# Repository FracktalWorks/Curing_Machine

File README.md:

# Curing_Machine
#Development Documentation:
## Setting up Raspberry Pi:
### Writing Image: 
[Raspbian Buster Lite](https://downloads.raspberrypi.org/raspbian_lite/images/raspbian_lite-2020-02-14/)

[Win32 Disk Imager](https://sourceforge.net/projects/win32diskimager/files/latest/download)

[SD Card Formatter](https://www.sdcard.org/downloads/formatter/sd-memory-card-formatter-for-windows-download/)

Clean with disk with SD card formatter selecting Quick Format and write Image to SD Card

### Setting up Pi
Add Wireless Settings & Enable SSH:
[link](https://www.tomshardware.com/reviews/raspberry-pi-headless-setup-how-to,6028.html)

```
country=IN
ctrl_interface=DIR=/var/run/wpa_supplicant GROUP=netdev
update_config=1

network={
scan_ssid=1
ssid="Fracktal 5"
psk="******"
}
```
WPA Supplicant known to work

### Installing dependencies
run ```sudo apt-get update --allow-releaseinfo-change``` in case of issues installing

pip3: ```sudo apt-get install python3-pip```

PyQt5: ```sudo apt-get install qt5-default pyqt5-dev pyqt5-dev-tools```

PyQT5: ```sudo apt install python3-pyqt5```

Git: ```sudo apt-get install git```

### Install 3.5inch touch screen driver

Reference: [link](https://www.waveshare.com/wiki/3.5inch_RPi_LCD_(A))

run: 
```
git clone https://github.com/waveshare/LCD-show.git
cd LCD-show
ls
chmod +x LCD35-show
./LCD35-show
```

### To make LCD Faster (Issue with ili based screens)

Changed ```sudo nano /boot/config.txt``` bottom to:

```
# Enable audio (loads snd_bcm2835)
dtparam=audio=on
dtoverlay=waveshare35a,fps=12,speed=16000000
#dtoverlay=ads7846,cs=1,penirq=17,penirq_pull=2,speed=1000000,keep_vref_on=1,swapxy=1,pmax=255,xohm$
hdmi_force_hotplug=1
#max_usb_current=1
hdmi_group=2
#hdmi_mode=1
hdmi_mode=87
hdmi_cvt 480 320 12 6 0 0 0
hdmi_drive=2
```
### Install Xwindows

```sudo apt-get install xserver-xorg-video-fbdev```

```sudo apt-get install xserver-xorg```

```sudo apt-get install xinit```

```sudo apt-get install x11-xserver-utils```

```sudo mv /usr/share/X11/xorg.conf.d/99-fbturbo.conf ~```  see [link](https://learn.adafruit.com/adafruit-pitft-3-dot-5-touch-screen-for-raspberry-pi/faq) for more information on this step

To test out working, use the following to start a PyQt5 program with ```sudo startx```
```#!/bin/sh

# /etc/X11/xinit/xinitrc
#
# global xinitrc file, used by all X sessions started by xinit (startx)
cd /home/pi/Julia2018Octoprint/venv/lib/python2.7/site-packages/octoprint_Julia2018ProDualABLTouchUI
sudo chmod +x Main.py
sudo python3 Main.py
# invoke global X session script
. /etc/X11/Xsession
```
###Removing boot messages
```sudo nano /boot/cmdline.txt```
change ```console=tty1``` to ```console=tty3``` 
Add ```loglevel=3``` to disable non-critical kernel log messages.
Add ```logo.nologo``` to the end of the line to remove the Raspberry PI logos from displaying
Press CTRL+X to exit and Y to save your changes.

### Changing the boot screen logo
Refeance : [link](https://www.hackster.io/kamaluddinkhan/changing-the-splash-screen-on-your-raspberry-pi-7aee31)
[link](https://raspberrypi.stackexchange.com/questions/100371/raspbian-buster-lite-splash-screen-instead-of-boot-messages-on-pi-3-model-b-a02)

The pi boots with a rainbow colour and many messages will be displayed during boot up.
to disable the boot message go to 
```sudo nano /boot/cmdline.txt```

in that file 
Add ```loglevel=3``` to disable non-critical kernel log messages.
Add ```logo.nologo``` to the end of the line to remove the Raspberry PI logos from displaying

now messages will not be shown 

### To add our logo 
install fbi
```sudo apt-get install fbi```

Create the file ```sudo nano /etc/systemd/system/splashscreen.service``` with the following content:

```
[Unit] 
Description=Splash screen 
DefaultDependencies=no 
After=local-fs.target 

[Service] 
ExecStart=/usr/bin/fbi -d /dev/fb0 --noverbose -a /home/pi/splash.png >/dev/null 2>&1
StandardInput=tty 
StandardOutput=tty 
[Install] 
WantedBy=sysinit.target

```
Replace `````/opt/splash.png````` with the path to the splash screen image as appropriate.

Enable the service to be run at boot by running as root:

```sudo systemctl enable splashscreen```

### Touch UI
install dependencies under ```sudo pip3```

#### Configure Startx (Xwindow manager which helps to show GUI on Raspbian os lite)

```sudo nano /etc/rc.local```
Add “startx” just before exit 0
```sudo nano /etc/X11/xinit/xinitrc```
Here you have to add the location of touch ui where it is saved and file name
Example 
```

#!/bin/sh

# /etc/X11/xinit/xinitrc
#
# global xinitrc file, used by all X sessions started by xinit (startx)
git clone https://github.com/FracktalWorks/Curing_Machine.git
cd /home/pi/Curing_Machine/code
sudo chmod +x curingMachine.py
sudo python3 curingMachine.py
# invoke global X session script
. /etc/X11/Xsession

```
Now when you do startx the GUI will boot up

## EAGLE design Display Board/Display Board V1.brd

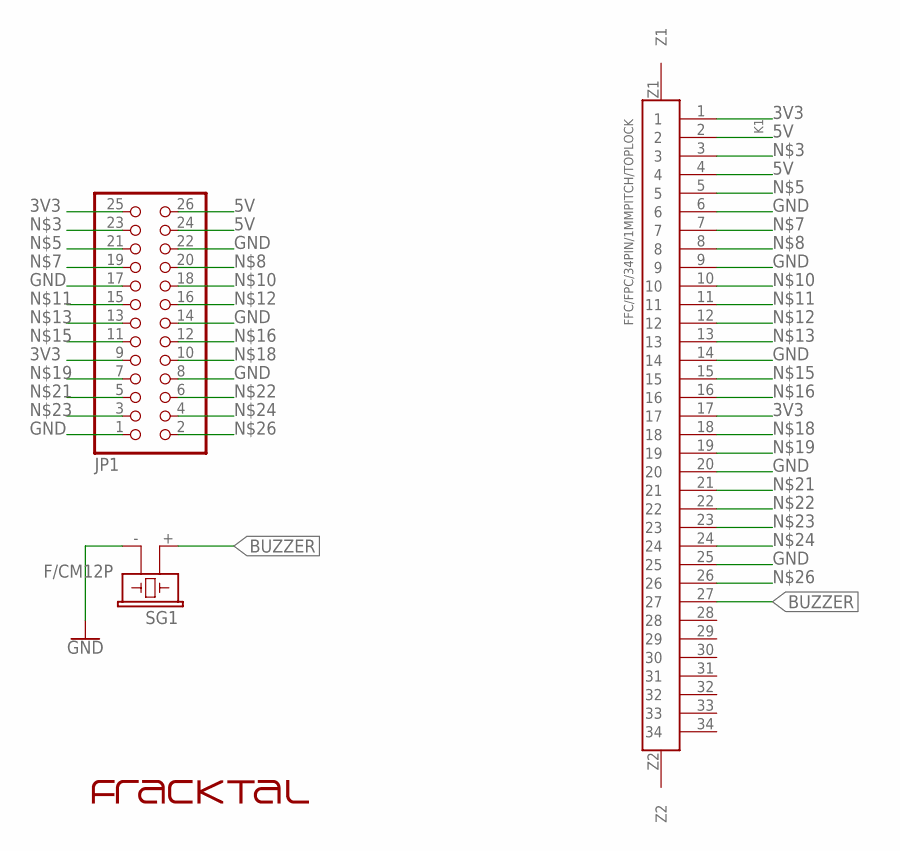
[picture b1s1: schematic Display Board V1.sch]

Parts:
JP1: PINHD-2X13; 2X13
K1: FFC/FPC/34PIN/1MMPITCH/TOPLOCK
SG1: F/CM12P
U$1: FRACKTALLOGO

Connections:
3V3: JP1.9, JP1.25, K1.1, K1.17
5V: JP1.24, JP1.26, K1.2, K1.4
BUZZER: K1.27, SG1.+ (1)
GND: JP1.1, JP1.8, JP1.14, JP1.17, JP1.22, K1.6, K1.9, K1.14, K1.20, K1.25, SG1.- (2)
unnamed: JP1.23, K1.3
unnamed: JP1.21, K1.5
unnamed: JP1.19, K1.7
unnamed: JP1.20, K1.8
unnamed: JP1.18, K1.10
unnamed: JP1.15, K1.11
unnamed: JP1.16, K1.12
unnamed: JP1.13, K1.13
unnamed: JP1.11, K1.15
unnamed: JP1.12, K1.16
unnamed: JP1.10, K1.18
unnamed: JP1.7, K1.19
unnamed: JP1.5, K1.21
unnamed: JP1.6, K1.22
unnamed: JP1.3, K1.23
unnamed: JP1.4, K1.24
unnamed: JP1.2, K1.26

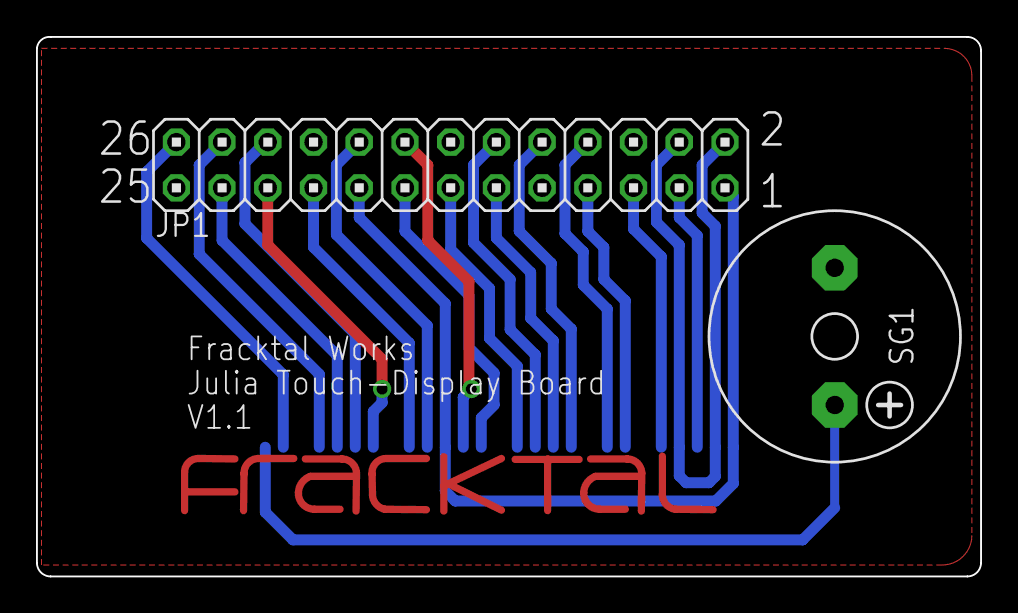
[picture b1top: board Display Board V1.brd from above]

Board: 2 copper layers, 52.5 x 30.0 mm, 4 parts (1 on the bottom side), 21 nets.

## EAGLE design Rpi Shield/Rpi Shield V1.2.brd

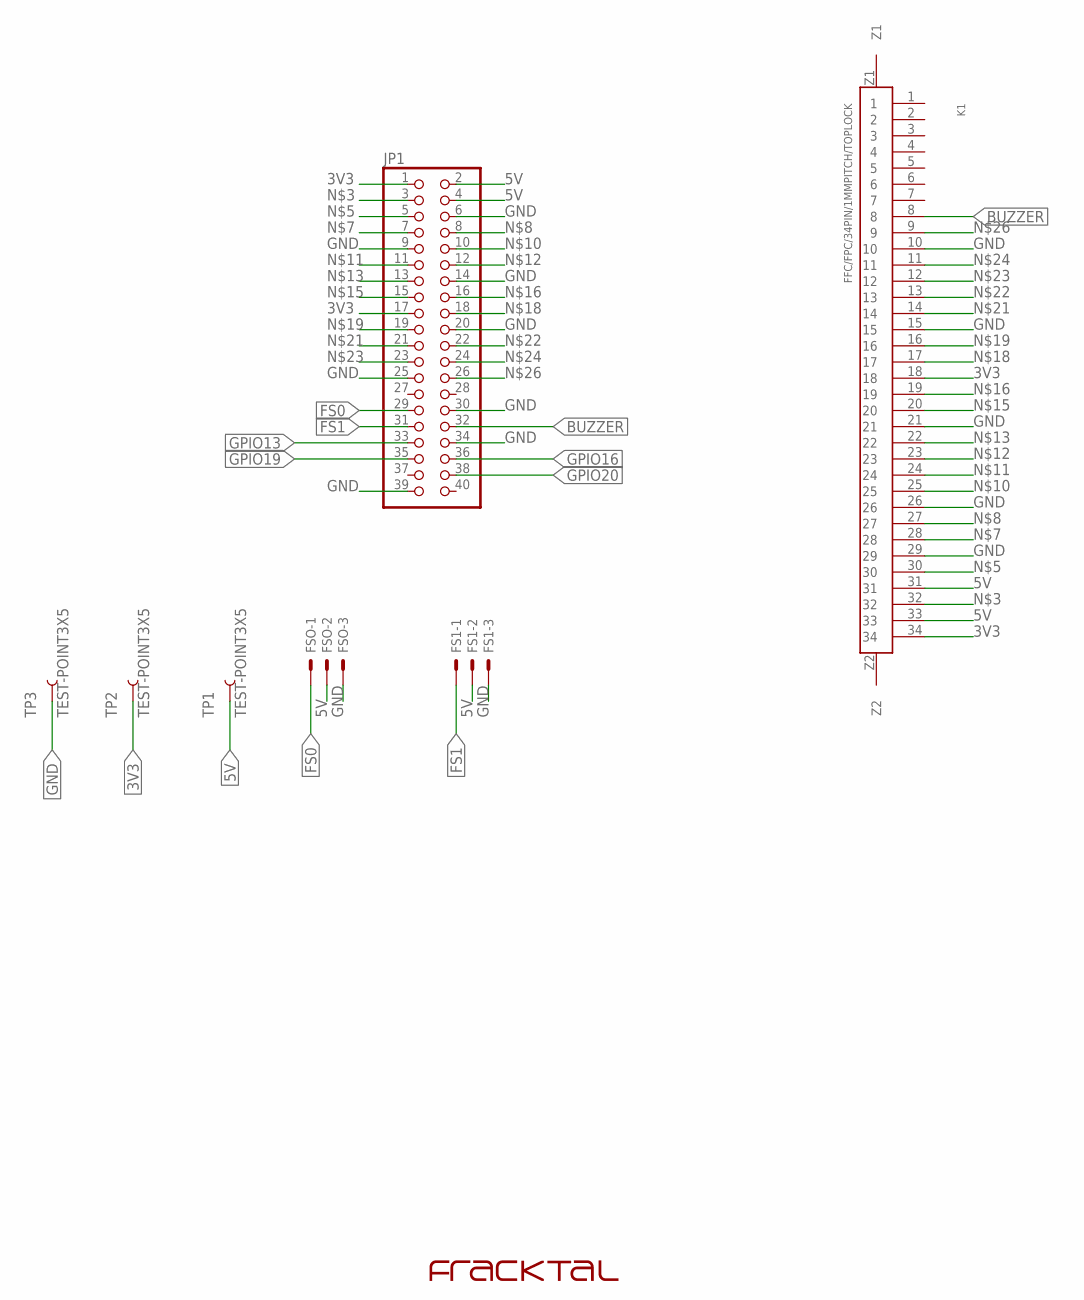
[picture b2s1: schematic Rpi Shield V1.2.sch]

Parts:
FS1: JST-XH-03-PIN-LONG-PAD; JST-XH-03-PACKAGE-LONG-PAD
FSO: JST-XH-03-PIN-LONG-PAD; JST-XH-03-PACKAGE-LONG-PAD
JP1: RASPBERRYPI_3B_GPIO
K1: FFC/FPC/34PIN/1MMPITCH/TOPLOCK
TP1, TP2, TP3: TEST-POINT3X5; PAD.03X.05
U$1: FRACKTALLOGO

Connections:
3V3: JP1.1, JP1.17, K1.18, K1.34, TP2.P$1
5V: FS1.2, FSO.2, JP1.2, JP1.4, K1.31, K1.33, TP1.P$1
BUZZER: JP1.32, K1.8
FS0: FSO.1, JP1.29
FS1: FS1.1, JP1.31
GND: FS1.3, FSO.3, JP1.6, JP1.9, JP1.14, JP1.20, JP1.25, JP1.30, JP1.34, JP1.39, K1.10, K1.15, K1.21, K1.26, K1.29, TP3.P$1
GPIO13: JP1.33
GPIO16: JP1.36
GPIO19: JP1.35
GPIO20: JP1.38
unnamed: JP1.3, K1.32
unnamed: JP1.5, K1.30
unnamed: JP1.7, K1.28
unnamed: JP1.8, K1.27
unnamed: JP1.10, K1.25
unnamed: JP1.11, K1.24
unnamed: JP1.12, K1.23
unnamed: JP1.13, K1.22
unnamed: JP1.15, K1.20
unnamed: JP1.16, K1.19
unnamed: JP1.18, K1.17
unnamed: JP1.19, K1.16
unnamed: JP1.21, K1.14
unnamed: JP1.22, K1.13
unnamed: JP1.23, K1.12
unnamed: JP1.24, K1.11
unnamed: JP1.26, K1.9

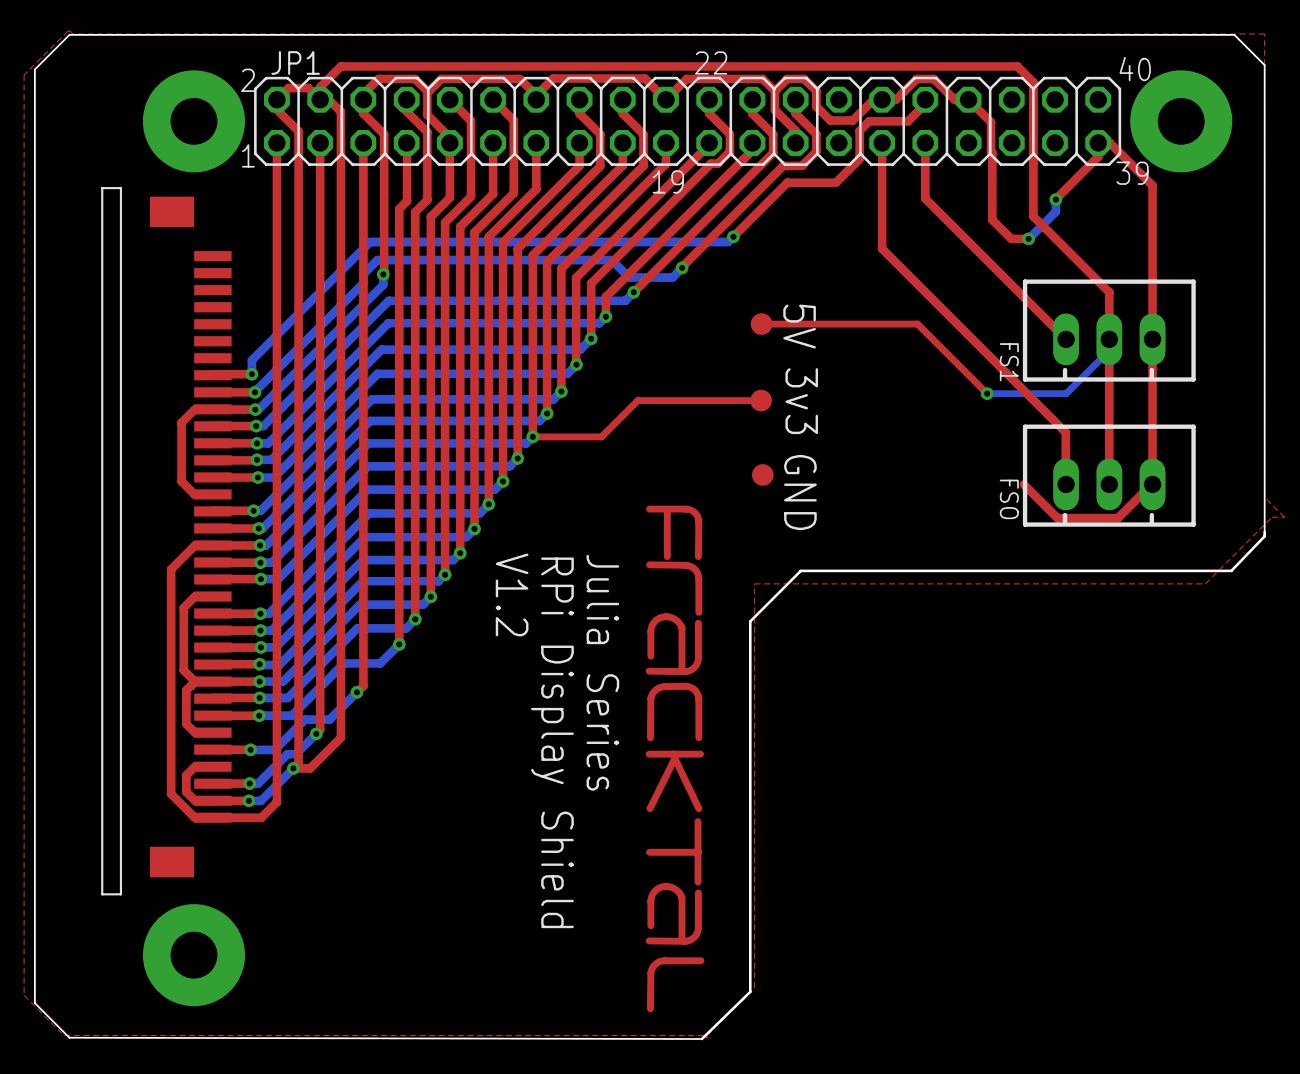
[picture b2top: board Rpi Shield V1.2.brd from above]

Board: 2 copper layers, 72.3 x 59.0 mm, 8 parts (0 on the bottom side), 23 nets.

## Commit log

2022-04-26 Inital files from https://github.com/FracktalWorks/Rpi-Display-Electronics
    Inital files from https://github.com/FracktalWorks/Rpi-Display-Electronics
2022-04-29 initial working ssr.py
2022-05-11 initial commit
    initial commit
2022-05-11 Bugfixes and Pycharm integration
2022-05-12 Keeping only code
    Keeping only code
2022-05-12 test
    test
2022-05-18 SSr.py
    ssr.py
2022-05-24 Code formatting
2022-05-25 Updated Code
2022-05-26 Initial Code Release
2022-05-26 Changed UI
2022-05-26 Max time changed
2022-05-27 testing
    testing
2022-05-30 Fixed turning off everything on Done
2022-05-30 Inverted Maglock Functionality
2022-05-30 Development = False
    Development = False
2022-05-30 Added few materials
    Added few materials like Clear, White. High temp, surgical guide. rigid 10K. Flexible 80A from formlabs
2022-05-30 Material.py update
    Material.py update
2022-06-02 added config folder
    added config folder
2022-06-02 Added WIFI capability
2022-06-02 DO NOT USE. QT version Issue
2022-06-02 --
    --
2022-06-02 reverted to before QT issue
    reverted to before QT issue
2022-06-02 test
    test Wifi changes and IP address moved
2022-06-02 Wifi spelling
    Wifi spelling
2022-06-02 Version error fixed
2022-06-02 Fixed Version Issue
2022-06-02 disaable hidden wifi
2022-06-02 wifi issue fix
2022-06-03 Backed up everything--Working
    Backed up everything--Working
2022-06-03 Working
    Working.

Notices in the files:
parts and their libraries:
SparkFun-PowerSymbols: Licensing: Creative Commons ShareAlike 4.0 International - https://creativecommons.org/licenses/by-sa/4.0
